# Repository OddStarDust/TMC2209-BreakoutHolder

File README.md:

# TMC2209-BreakoutHolder
TMC2209 plug and play breakout board. The porpuse of this pcb is to make an easy way to test stepper drivers

An ultra-compact, high-reliability breakout board designed to be holded on to the bottom of stepper motor nema 17. **TMC2209**, **A4988**, and **DRV8825** stepper driver modules (standard StepStick footprint). Engineered for 3D printers, CNC machinery, and custom robotics projects requiring secure connections and transient voltage protection.

---

## 📸 Overview & Rendering

| Board Top View | 3D Render |
| :---: | :---: |
|  |  |

---

## ✨ Key Features

* **Voltage Spike Protection (VMOT):** Integrated footprint for a $100\\mu\\text{F} / 35\\text{V}$ decoupling electrolytic capacitor to absorb back-EMF spikes and preserve driver life.
* **Secure Interconnects:** Utilizes standard **JST connectors** (2-pin power/signals, 4-pin motor coil) to prevent accidental disconnects during high-vibration operation.
* **Universal StepStick Socket:** Compatible with standard 2.54mm header StepStick drivers (TMC2209, A4988, DRV8825, etc.).
* **Turnkey Manufacturing Ready:** Includes pre-configured Gerber, Drill, BOM, and CPL files tested for 1-click fabrication on **JLCPCB** and **PCBWay**.
* **Clean Signal Routing:** Designed with optimized ground planes and thermal relief pads for easy manual or automated soldering.

---

## 📐 Pinout & Connection Diagram

```text
               +-----------------------+
               |     TMC2209 DRIVER    |
               |       SOCKETS         |
               +-----------------------+
              /                         \\
   [VMOT / GND]                          [STEP / DIR / EN]
  (2-Pin JST Input)                     (2.54mm Header Pins)
              \\                         /
               +-----------------------+
               |   MOTOR COILS (4-Pin) |
               +-----------------------+

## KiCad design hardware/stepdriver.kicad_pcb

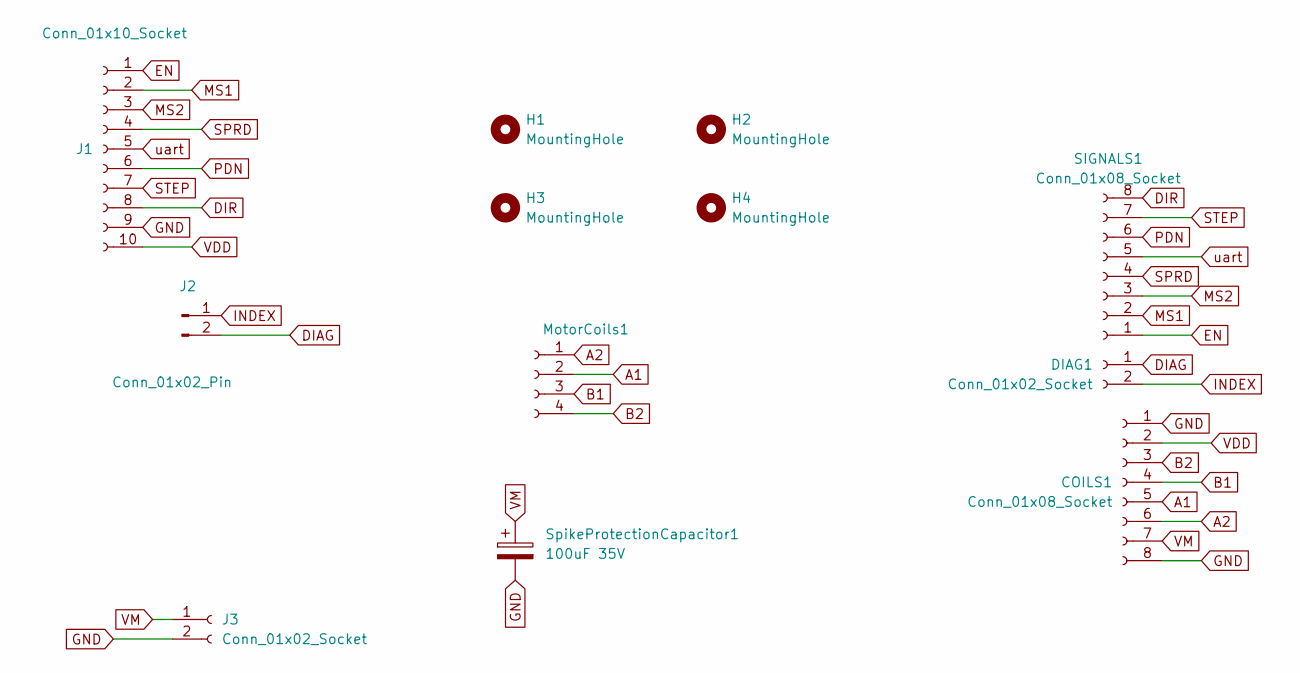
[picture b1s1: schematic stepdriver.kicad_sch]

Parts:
COILS1: Conn_01x08_Socket; PinSocket_1x08_P2.54mm_Vertical
DIAG1: Conn_01x02_Socket; PinSocket_1x02_P2.54mm_Vertical
H1, H2, H3, H4: MountingHole; MountingHole_2.7mm_M2.5_ISO14580_Pad
J1: Conn_01x10_Socket; JST_PH_S10B-PH-K_1x10_P2.00mm_Horizontal
J2: Conn_01x02_Pin; JST_EH_S2B-EH_1x02_P2.50mm_Horizontal
J3: Conn_01x02_Socket; JST_EH_S2B-EH_1x02_P2.50mm_Horizontal
MotorCoils1: Conn_01x04_Socket; JST_EH_S4B-EH_1x04_P2.50mm_Horizontal
SIGNALS1: Conn_01x08_Socket; PinSocket_1x08_P2.54mm_Vertical
SpikeProtectionCapacitor1: 100uF 35V; CP_Radial_D6.3mm_P2.50mm

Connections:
A1: COILS1.5, MotorCoils1.2
A2: COILS1.6, MotorCoils1.1
B1: COILS1.4, MotorCoils1.3
B2: COILS1.3, MotorCoils1.4
DIAG: DIAG1.1, J2.2
DIR: J1.8, SIGNALS1.8
EN: J1.1, SIGNALS1.1
GND: COILS1.1, COILS1.8, J1.9, J3.2, SpikeProtectionCapacitor1.2; also elsewhere on the board
INDEX: DIAG1.2, J2.1
MS1: J1.2, SIGNALS1.2
MS2: J1.3, SIGNALS1.3
PDN: J1.6, SIGNALS1.6
SPRD: J1.4, SIGNALS1.4
STEP: J1.7, SIGNALS1.7
VDD: COILS1.2, J1.10
VM: COILS1.7, J3.1, SpikeProtectionCapacitor1.1; also elsewhere on the board
uart: J1.5, SIGNALS1.5

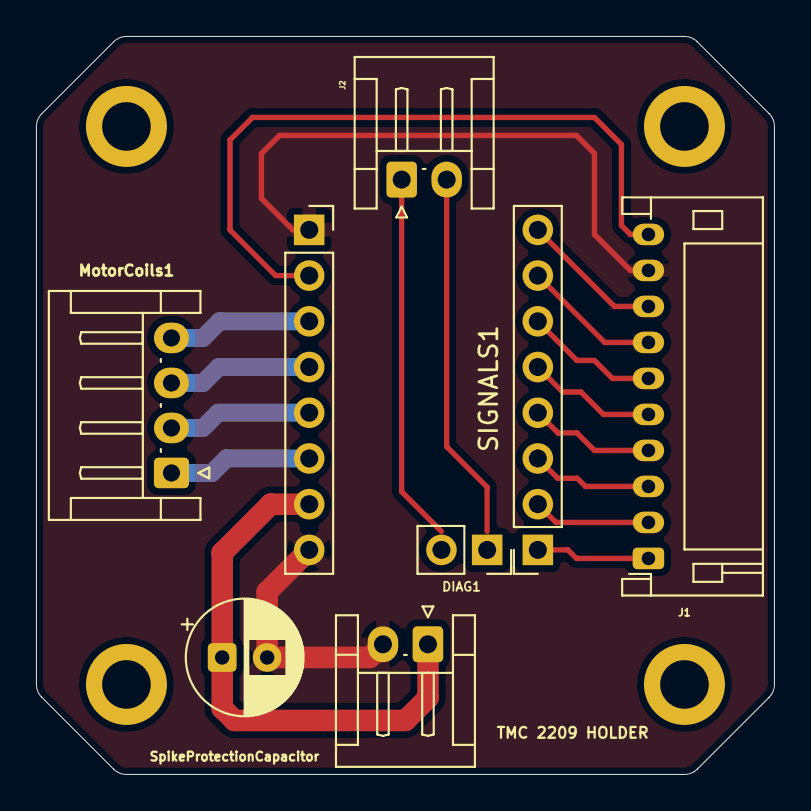
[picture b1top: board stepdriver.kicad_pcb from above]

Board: 2 copper layers, 41.0 x 41.0 mm, 12 parts (0 on the bottom side), 17 nets.

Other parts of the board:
SpikeProtectionCapacitor: 100uF 35V; CP_Radial_D6.3mm_P2.50mm

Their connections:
GND: SpikeProtectionCapacitor.2; also elsewhere on the board
VM: SpikeProtectionCapacitor.1; also elsewhere on the board

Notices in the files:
README.md:
License: CERN-OHL-W-v2
